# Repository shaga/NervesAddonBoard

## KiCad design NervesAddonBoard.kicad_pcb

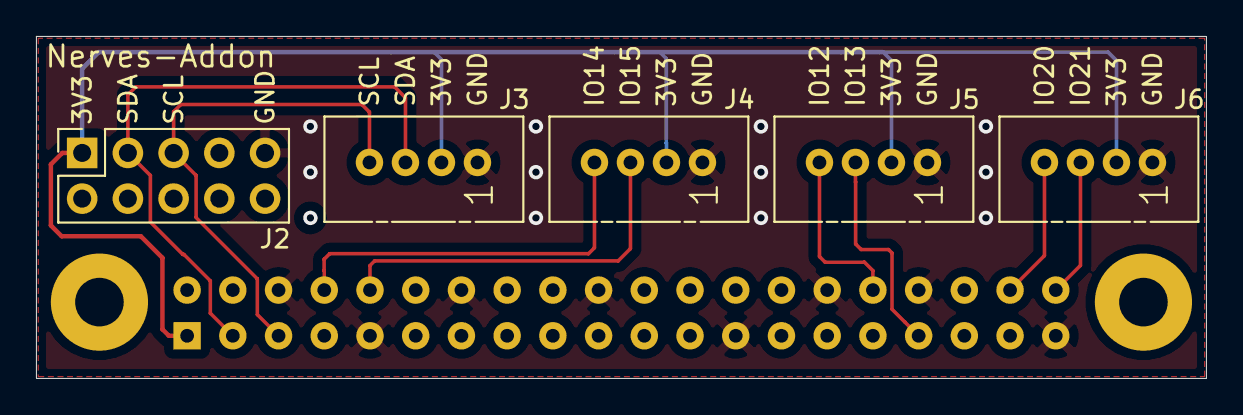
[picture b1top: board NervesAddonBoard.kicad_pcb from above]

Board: 2 copper layers, 65.0 x 19.0 mm, 6 parts (0 on the bottom side), 10 nets.

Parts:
J1: Conn_02x20_Odd_Even; RPi2x20THL
J2: Conn_02x05_Odd_Even; Socket_Strip_Straight_2x05_Pitch2.54mm
J3, J4, J5, J6: Grove_4pin_connector; Grove_1x04

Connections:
+3V3: J1.1, J2.1, J3.2, J4.2, J5.2, J6.2
/IO12_PWM0: J1.32, J5.4
/IO13_PWM1: J1.33, J5.3
/IO14_TxD: J1.8, J4.4
/IO15_RxD: J1.10, J4.3
/IO20: J1.38, J6.4
/IO21: J1.40, J6.3
/SCL: J1.5, J2.5, J3.4
/SDA: J1.3, J2.3, J3.3
GND: J1.6, J1.9, J1.14, J1.20, J1.25, J1.30, J1.34, J1.39, J2.9, J3.1, J4.1, J5.1, J6.1

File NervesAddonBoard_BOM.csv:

"ID";"参照記号";"パッケージ";"数";"名称";"Supplier and ref";
1;"IC1";"SOIC127P600X175-8N";1;"ATECC608A-SSHDA-B";;;
2;"REF**,REF**,REF**,REF**";"MountingHole_2.7mm_Pad";4;"MountingHole_2.7mm_Pad";;;
3;"J1";"RPi2x20THL";1;"Conn_02x20_Odd_Even";;;
4;"C1";"C_0402";1;"C";;;
5;"J2,J3,J4";"Grove_1x04_90";3;"Grove_4pin_connector";;;

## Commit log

2019-06-23 add data
2019-08-29 add silk
2019-08-29 update gerber
2019-08-29 change connector footprint
2019-09-07 create project directory and move files to new directory
2019-09-07 add project symbole/footprint libs
2019-09-07 change LICENSE from Apache License to MIT License
